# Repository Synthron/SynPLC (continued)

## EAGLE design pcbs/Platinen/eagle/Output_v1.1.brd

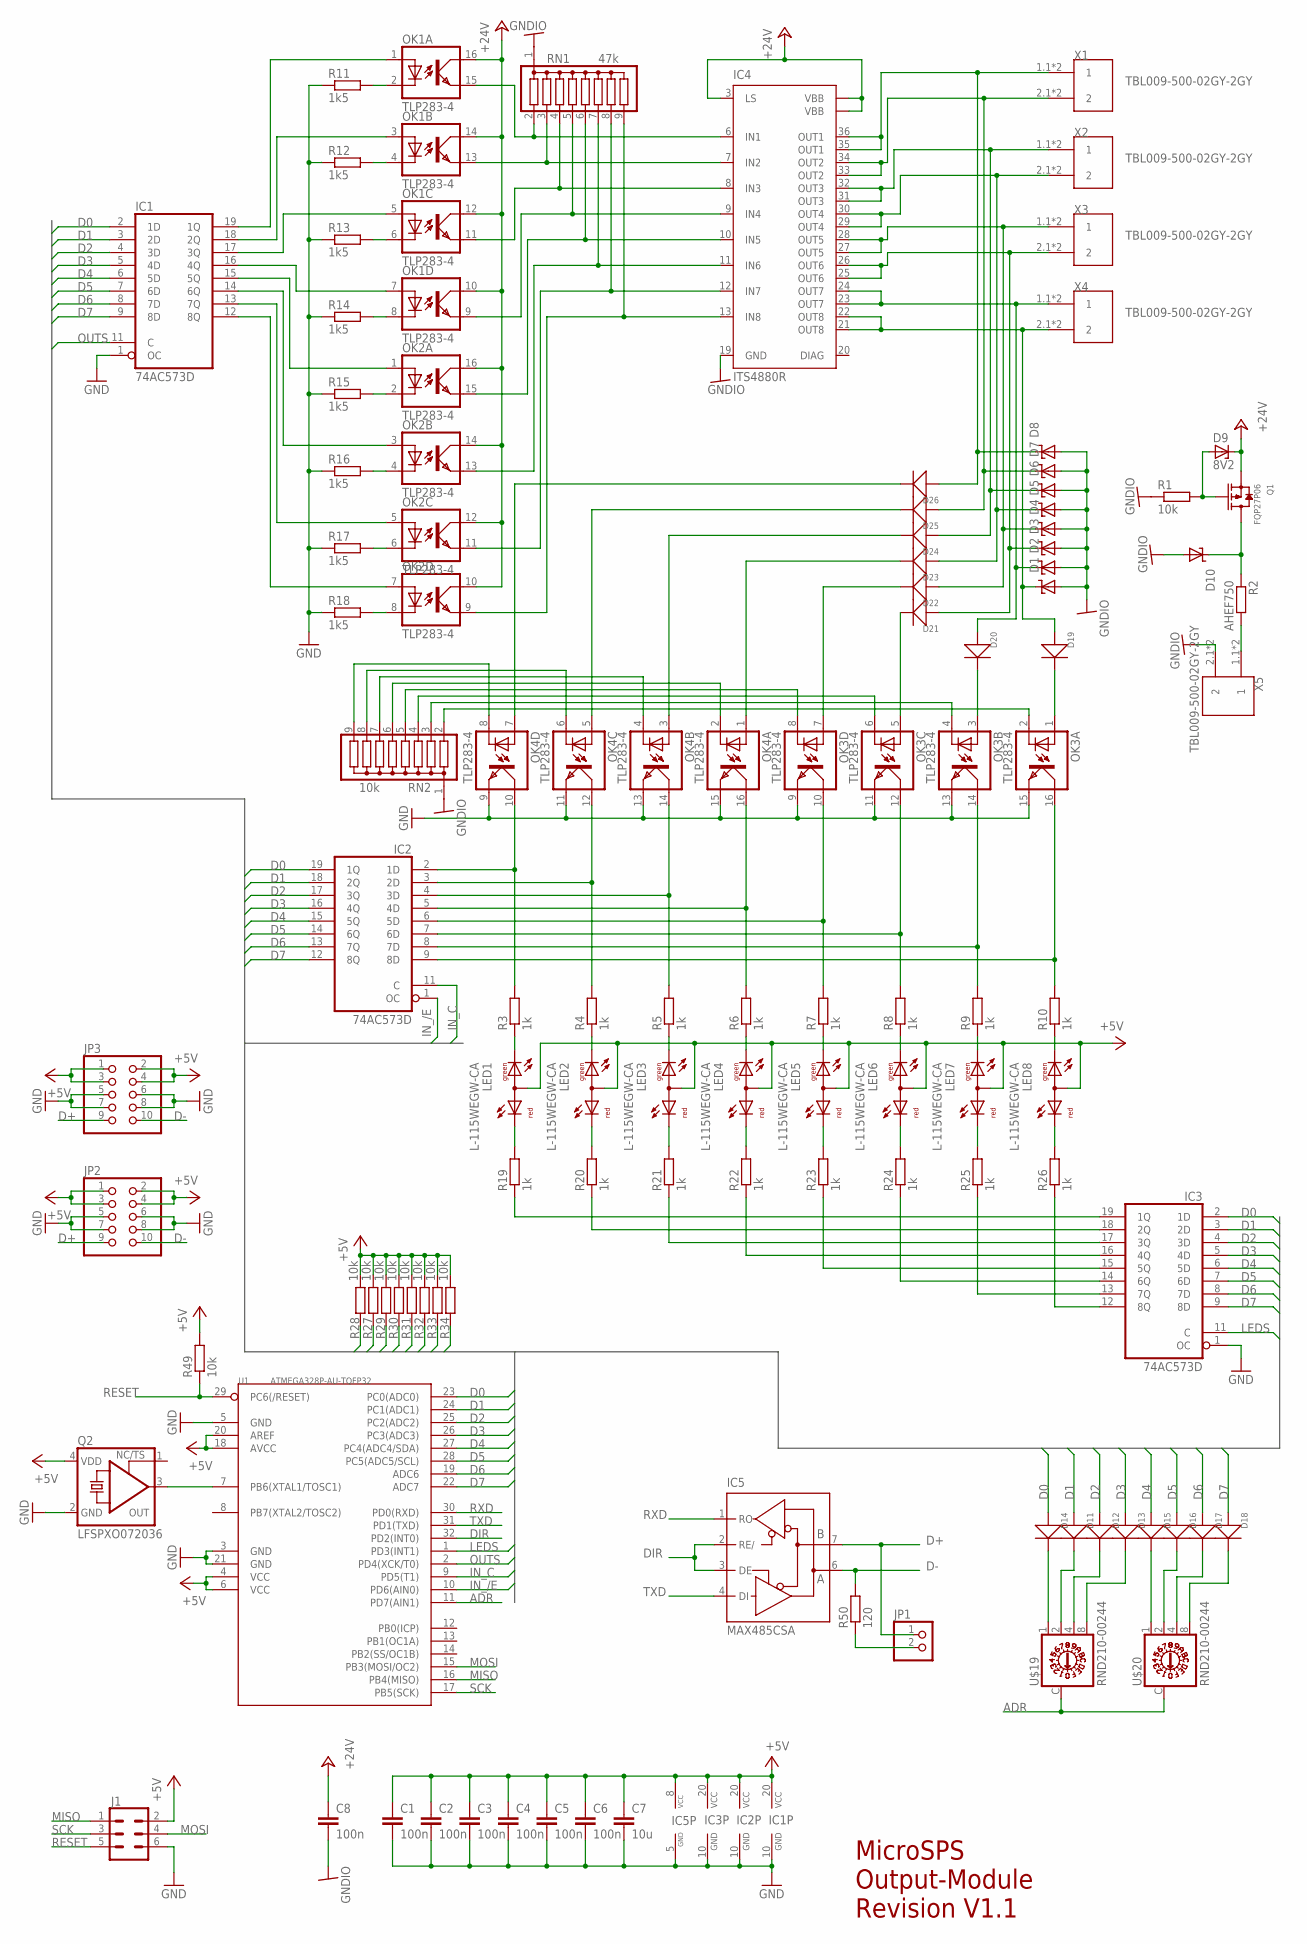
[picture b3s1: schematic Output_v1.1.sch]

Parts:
C1, C2, C3, C4, C5, C6, C8: 100n; C0805
C7: 10u; C0805
D1, D2, D3, D4, D5, D6, D7, D8, D10: SUPPRESSOR-SMBJ; SMBJ
D9: 8V2; SOD80C
D11, D12, D13, D14, D15, D16, D17, D18, D19, D20, D21, D22, D23, D24, D25, D26: DIODE'1N4148-SMD'; LL-34
IC1, IC2, IC3: 74AC573D; SO20W
IC4: ITS4880R; PG-DSO-36
IC5: MAX485CSA; SO08
J1: CONN_03X2FEMALE_SMD; 2X3_SMD
JP1: PINHD-1X2; 1X02
JP2, JP3: PINHD-2X5/90; 2X05/90
LED1, LED2, LED3, LED4, LED5, LED6, LED7, LED8: L-115WEGW-CA; DUOLED-A-3MM
OK1, OK2, OK3, OK4: TLP283-4; MINI-FLAT-16
Q1: FQP27P06; TO-220V
Q2: LFSPXO072036; 5.0X3.2_KXO-56
R1, R27, R28, R29, R30, R31, R32, R33, R34, R49: 10k; R0805
R2: AHEF750; 0204/7
R3, R4, R5, R6, R7, R8, R9, R10, R19, R20, R21, R22, R23, R24, R25, R26: 1k; R0805
R11, R12, R13, R14, R15, R16, R17, R18: 1k5; R0805
R50: 120; R0805
RN1: 47k; SIL9
RN2: 10k; SIL9
U1: ATMEGA328P-AU-TQFP32; TQFP32-0.8-7X7MM
U$19, U$20: RND210-00244
X1, X2, X3, X4, X5: TBL009-500-02GY-2GY

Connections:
+5V: C1.1, C2.1, C3.1, C4.1, C5.1, C6.1, C7.1, IC1.20 (VCC), IC2.20 (VCC), IC3.20 (VCC), IC5.8 (VCC), J1.2, JP2.1, JP2.2, JP2.3, JP2.4, JP3.1, JP3.2, JP3.3, JP3.4, LED1.2 (A), LED2.2 (A), LED3.2 (A), LED4.2 (A), LED5.2 (A), LED6.2 (A), LED7.2 (A), LED8.2 (A), Q2.4 (VDD), R27.2, R28.2, R29.2, R30.2, R31.2, R32.2, R33.2, R34.2, R49.2, U1.4 (VCC), U1.6 (VCC), U1.18 (AVCC), U1.20 (AREF)
+24V: C8.1, D9.C, IC4.3 (LS), IC4.TH@1 (VBB), IC4.TH@2 (VBB), OK1.10 (COL), OK1.12 (COL), OK1.14 (COL), OK1.16 (COL), OK2.10 (COL), OK2.12 (COL), OK2.14 (COL), OK2.16 (COL), Q1.3 (S)
ADR: U1.11 (PD7(AIN1)), U$19.C, U$20.C
D0: D14.A (+), IC1.2 (1D), IC2.19 (1Q), IC3.2 (1D), R28.1, U1.23 (PC0(ADC0))
D1: D11.A (+), IC1.3 (2D), IC2.18 (2Q), IC3.3 (2D), R27.1, U1.24 (PC1(ADC1))
D2: D12.A (+), IC1.4 (3D), IC2.17 (3Q), IC3.4 (3D), R29.1, U1.25 (PC2(ADC2))
D3: D13.A (+), IC1.5 (4D), IC2.16 (4Q), IC3.5 (4D), R30.1, U1.26 (PC3(ADC3))
D4: D15.A (+), IC1.6 (5D), IC2.15 (5Q), IC3.6 (5D), R31.1, U1.27 (PC4(ADC4/SDA))
D5: D16.A (+), IC1.7 (6D), IC2.14 (6Q), IC3.7 (6D), R32.1, U1.28 (PC5(ADC5/SCL))
D6: D17.A (+), IC1.8 (7D), IC2.13 (7Q), IC3.8 (7D), R33.1, U1.19 (ADC6)
D7: D18.A (+), IC1.9 (8D), IC2.12 (8Q), IC3.9 (8D), R34.1, U1.22 (ADC7)
D+: IC5.7 (B), JP1.1, JP2.9, JP3.9
D-: IC5.6 (A), JP2.10, JP3.10, R50.2
DIR: IC5.2 (RE/), IC5.3 (DE), U1.32 (PD2(INT0))
GND: C1.2, C2.2, C3.2, C4.2, C5.2, C6.2, C7.2, IC1.1 (OC), IC1.10 (GND), IC2.10 (GND), IC3.1 (OC), IC3.10 (GND), IC5.5 (GND), J1.6, JP2.5, JP2.6, JP2.7, JP2.8, JP3.5, JP3.6, JP3.7, JP3.8, OK3.9 (EMIT), OK3.11 (EMIT), OK3.13 (EMIT), OK3.15 (EMIT), OK4.9 (EMIT), OK4.11 (EMIT), OK4.13 (EMIT), OK4.15 (EMIT), Q2.2 (GND), R11.1, R12.1, R13.1, R14.1, R15.1, R16.1, R17.1, R18.1, U1.3 (GND), U1.5 (GND), U1.21 (GND)
GNDIO: C8.2, D1.A, D2.A, D3.A, D4.A, D5.A, D6.A, D7.A, D8.A, D10.A, IC4.19 (GND), R1.1, RN1.1, RN2.1, X5.2.1 (2), X5.2.2 (2)
IN_/E: IC2.1 (OC), U1.10 (PD6(AIN0))
IN_C: IC2.11 (C), U1.9 (PD5(T1))
LEDS: IC3.11 (C), U1.1 (PD3(INT1))
MISO: J1.1, U1.16 (PB4(MISO))
MOSI: J1.4, U1.15 (PB3(MOSI/OC2))
unnamed: IC4.6 (IN1), OK1.15 (EMIT), RN1.2
unnamed: IC4.7 (IN2), OK1.13 (EMIT), RN1.3
unnamed: IC4.8 (IN3), OK1.11 (EMIT), RN1.4
unnamed: IC4.9 (IN4), OK1.9 (EMIT), RN1.5
unnamed: IC4.10 (IN5), OK2.15 (EMIT), RN1.6
unnamed: IC4.11 (IN6), OK2.13 (EMIT), RN1.7
unnamed: IC4.12 (IN7), OK2.11 (EMIT), RN1.8
unnamed: IC4.13 (IN8), OK2.9 (EMIT), RN1.9
unnamed: LED1.1 (CG), R3.1
unnamed: LED2.1 (CG), R4.1
unnamed: LED3.1 (CG), R5.1
unnamed: LED4.1 (CG), R6.1
unnamed: LED5.1 (CG), R7.1
unnamed: LED6.1 (CG), R8.1
unnamed: LED7.1 (CG), R9.1
unnamed: LED8.1 (CG), R10.1
unnamed: OK3.2 (C), RN2.2
unnamed: OK3.4 (C), RN2.3
unnamed: OK3.6 (C), RN2.4
unnamed: OK3.8 (C), RN2.5
unnamed: OK4.2 (C), RN2.6
unnamed: OK4.4 (C), RN2.7
unnamed: OK4.6 (C), RN2.8
unnamed: OK4.8 (C), RN2.9
unnamed: D10.C, Q1.2 (D), R2.1
unnamed: D9.A, Q1.1 (G), R1.2
unnamed: D1.C, D19.A (+), IC4.21 (OUT8), IC4.22 (OUT8), X4.2.1 (2), X4.2.2 (2)
unnamed: R2.2, X5.1.1 (1), X5.1.2 (1)
unnamed: D2.C, D20.A (+), IC4.23 (OUT7), IC4.24 (OUT7), X4.1.1 (1), X4.1.2 (1)
unnamed: D3.C, D21.A (+), IC4.25 (OUT6), IC4.26 (OUT6), X3.2.1 (2), X3.2.2 (2)
unnamed: D4.C, D22.A (+), IC4.27 (OUT5), IC4.28 (OUT5), X3.1.1 (1), X3.1.2 (1)
unnamed: D5.C, D23.A (+), IC4.29 (OUT4), IC4.30 (OUT4), X2.2.1 (2), X2.2.2 (2)
unnamed: D6.C, D24.A (+), IC4.31 (OUT3), IC4.32 (OUT3), X2.1.1 (1), X2.1.2 (1)
unnamed: D7.C, D25.A (+), IC4.33 (OUT2), IC4.34 (OUT2), X1.2.1 (2), X1.2.2 (2)
unnamed: D8.C, D26.A (+), IC4.35 (OUT1), IC4.36 (OUT1), X1.1.1 (1), X1.1.2 (1)
unnamed: IC2.2 (1D), OK4.10 (COL), R3.2
unnamed: IC2.3 (2D), OK4.12 (COL), R4.2
unnamed: IC2.4 (3D), OK4.14 (COL), R5.2
unnamed: IC2.5 (4D), OK4.16 (COL), R6.2
unnamed: IC2.6 (5D), OK3.10 (COL), R7.2
unnamed: IC2.7 (6D), OK3.12 (COL), R8.2
unnamed: IC2.8 (7D), OK3.14 (COL), R9.2
unnamed: IC2.9 (8D), OK3.16 (COL), R10.2
unnamed: IC3.19 (1Q), R19.1
unnamed: IC3.18 (2Q), R20.1
unnamed: IC3.17 (3Q), R21.1
unnamed: IC3.16 (4Q), R22.1
unnamed: IC3.15 (5Q), R23.1
unnamed: IC3.14 (6Q), R24.1
unnamed: IC3.13 (7Q), R25.1
unnamed: IC3.12 (8Q), R26.1
unnamed: LED1.3 (CR), R19.2
unnamed: LED2.3 (CR), R20.2
unnamed: OK1.2 (C), R11.2
unnamed: OK1.4 (C), R12.2
unnamed: OK1.6 (C), R13.2
unnamed: OK1.8 (C), R14.2
unnamed: OK2.2 (C), R15.2
unnamed: LED3.3 (CR), R21.2
unnamed: OK2.4 (C), R16.2
unnamed: OK2.6 (C), R17.2
unnamed: OK2.8 (C), R18.2
unnamed: IC1.17 (3Q), OK1.5 (A)
unnamed: IC1.18 (2Q), OK1.3 (A)
unnamed: IC1.19 (1Q), OK1.1 (A)
unnamed: IC1.16 (4Q), OK1.7 (A)
unnamed: IC1.15 (5Q), OK2.1 (A)
unnamed: IC1.14 (6Q), OK2.3 (A)
unnamed: IC1.13 (7Q), OK2.5 (A)
unnamed: IC1.12 (8Q), OK2.7 (A)
unnamed: LED4.3 (CR), R22.2
unnamed: LED5.3 (CR), R23.2
unnamed: LED6.3 (CR), R24.2
unnamed: LED7.3 (CR), R25.2
unnamed: LED8.3 (CR), R26.2
unnamed: D19.C (-), OK3.1 (A)
unnamed: D20.C (-), OK3.3 (A)
unnamed: D21.C (-), OK3.5 (A)
unnamed: D22.C (-), OK3.7 (A)
unnamed: D23.C (-), OK4.1 (A)
unnamed: D24.C (-), OK4.3 (A)
unnamed: D25.C (-), OK4.5 (A)
unnamed: D26.C (-), OK4.7 (A)
unnamed: Q2.3 (OUT), U1.7 (PB6(XTAL1/TOSC1))
unnamed: JP1.2, R50.1
unnamed: D14.C (-), U$19.1
unnamed: D11.C (-), U$19.2
unnamed: D12.C (-), U$19.4
unnamed: D13.C (-), U$19.8
unnamed: D15.C (-), U$20.1
unnamed: D16.C (-), U$20.2
unnamed: D17.C (-), U$20.4
unnamed: D18.C (-), U$20.8
OUTS: IC1.11 (C), U1.2 (PD4(XCK/T0))
RESET: J1.5, R49.1, U1.29 (PC6(/RESET))
RXD: IC5.1 (RO), U1.30 (PD0(RXD))
SCK: J1.3, U1.17 (PB5(SCK))
TXD: IC5.4 (DI), U1.31 (PD1(TXD))

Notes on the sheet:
MicroSPS Output-Module Revision V1.1

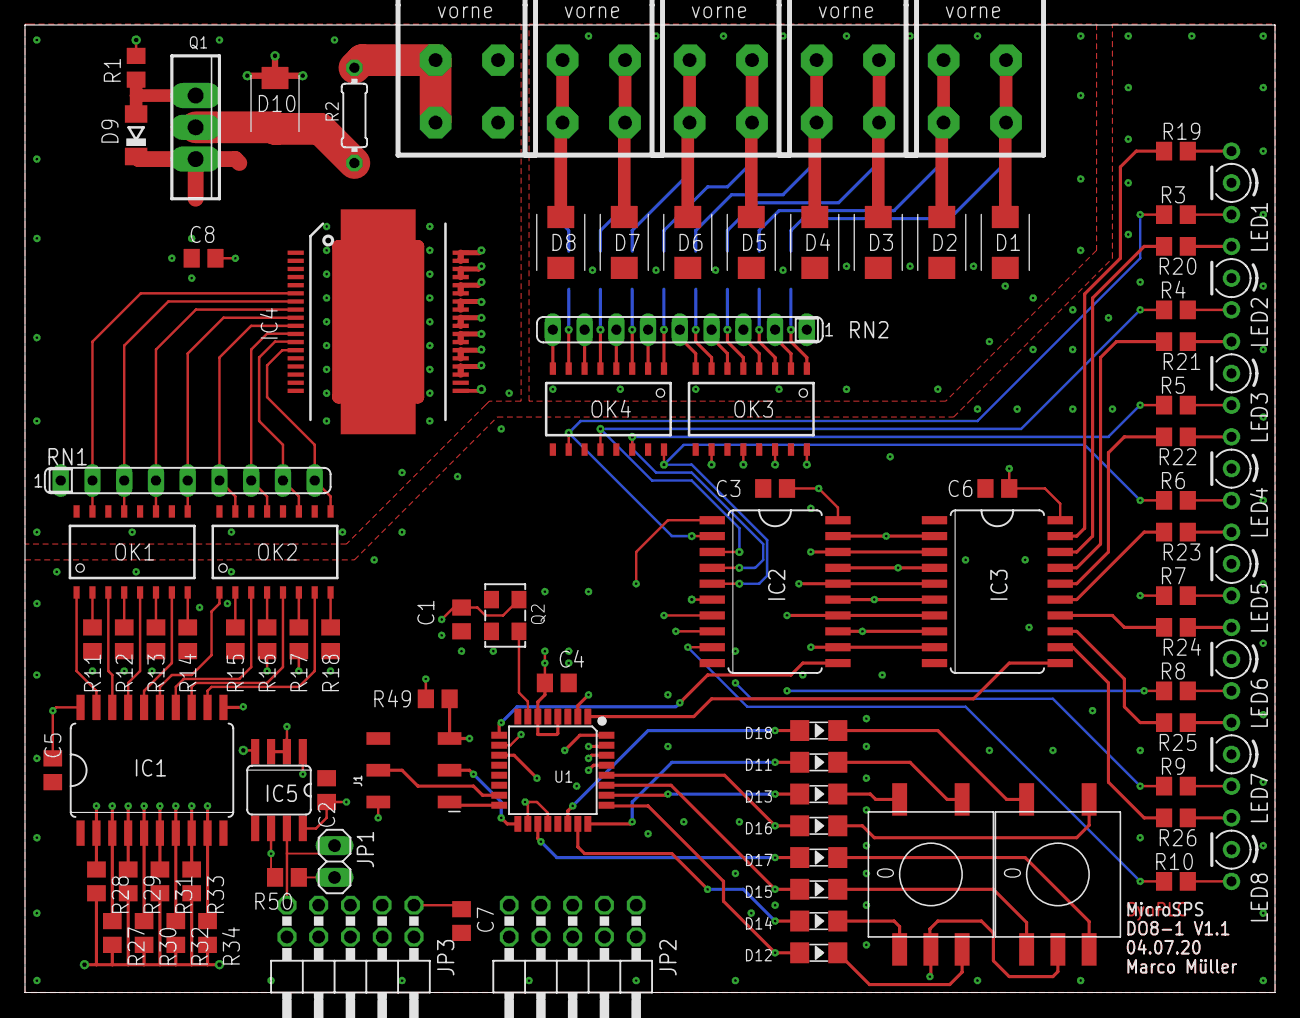
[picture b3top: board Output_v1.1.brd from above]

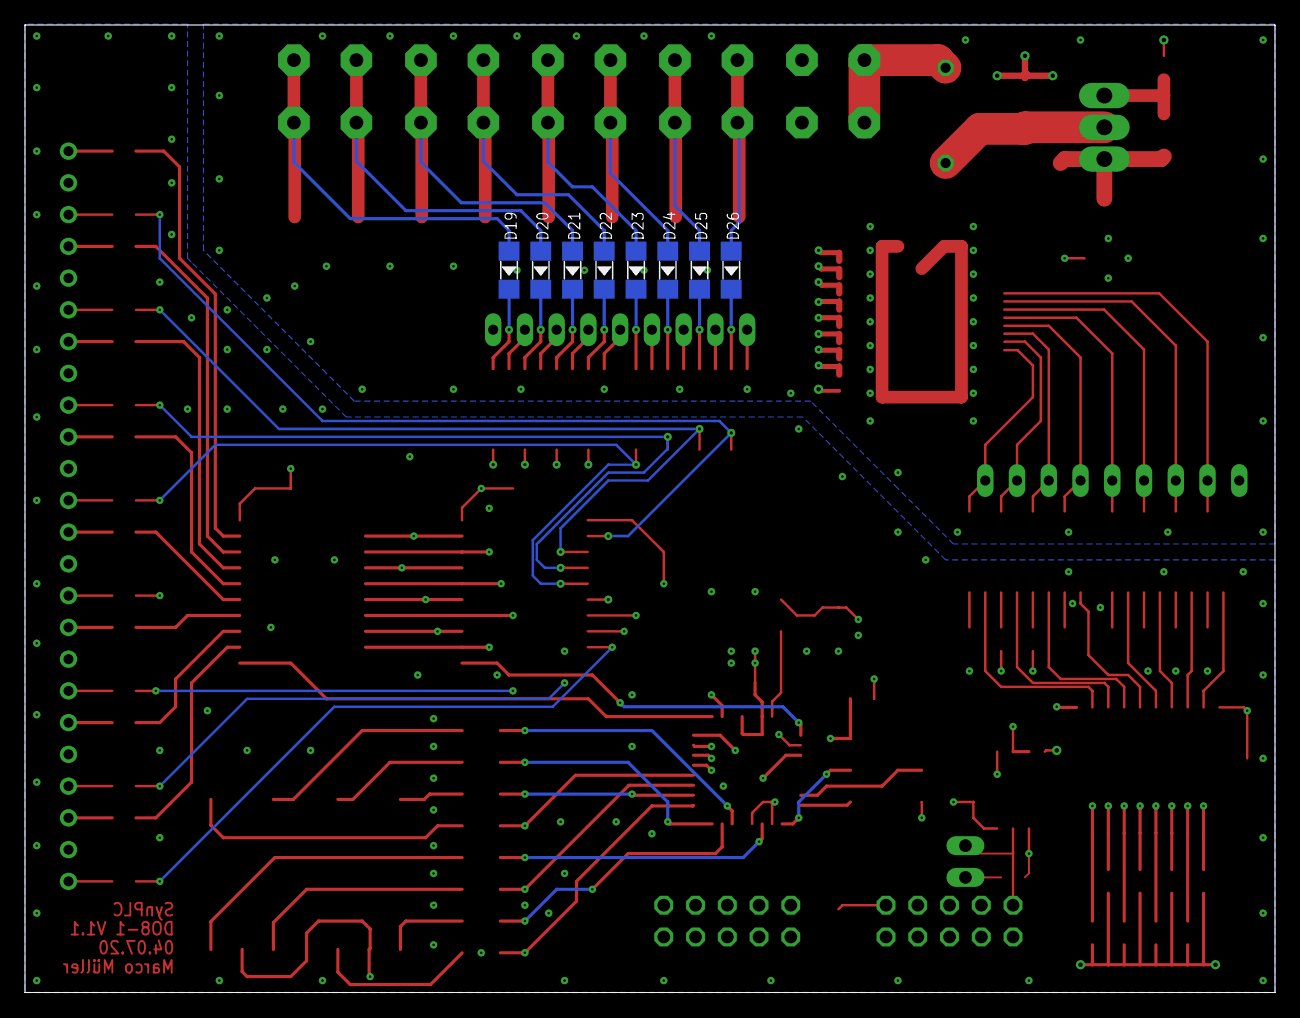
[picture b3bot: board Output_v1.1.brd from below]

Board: 4 copper layers, 100.0 x 77.4 mm, 103 parts (8 on the bottom side), 119 nets.

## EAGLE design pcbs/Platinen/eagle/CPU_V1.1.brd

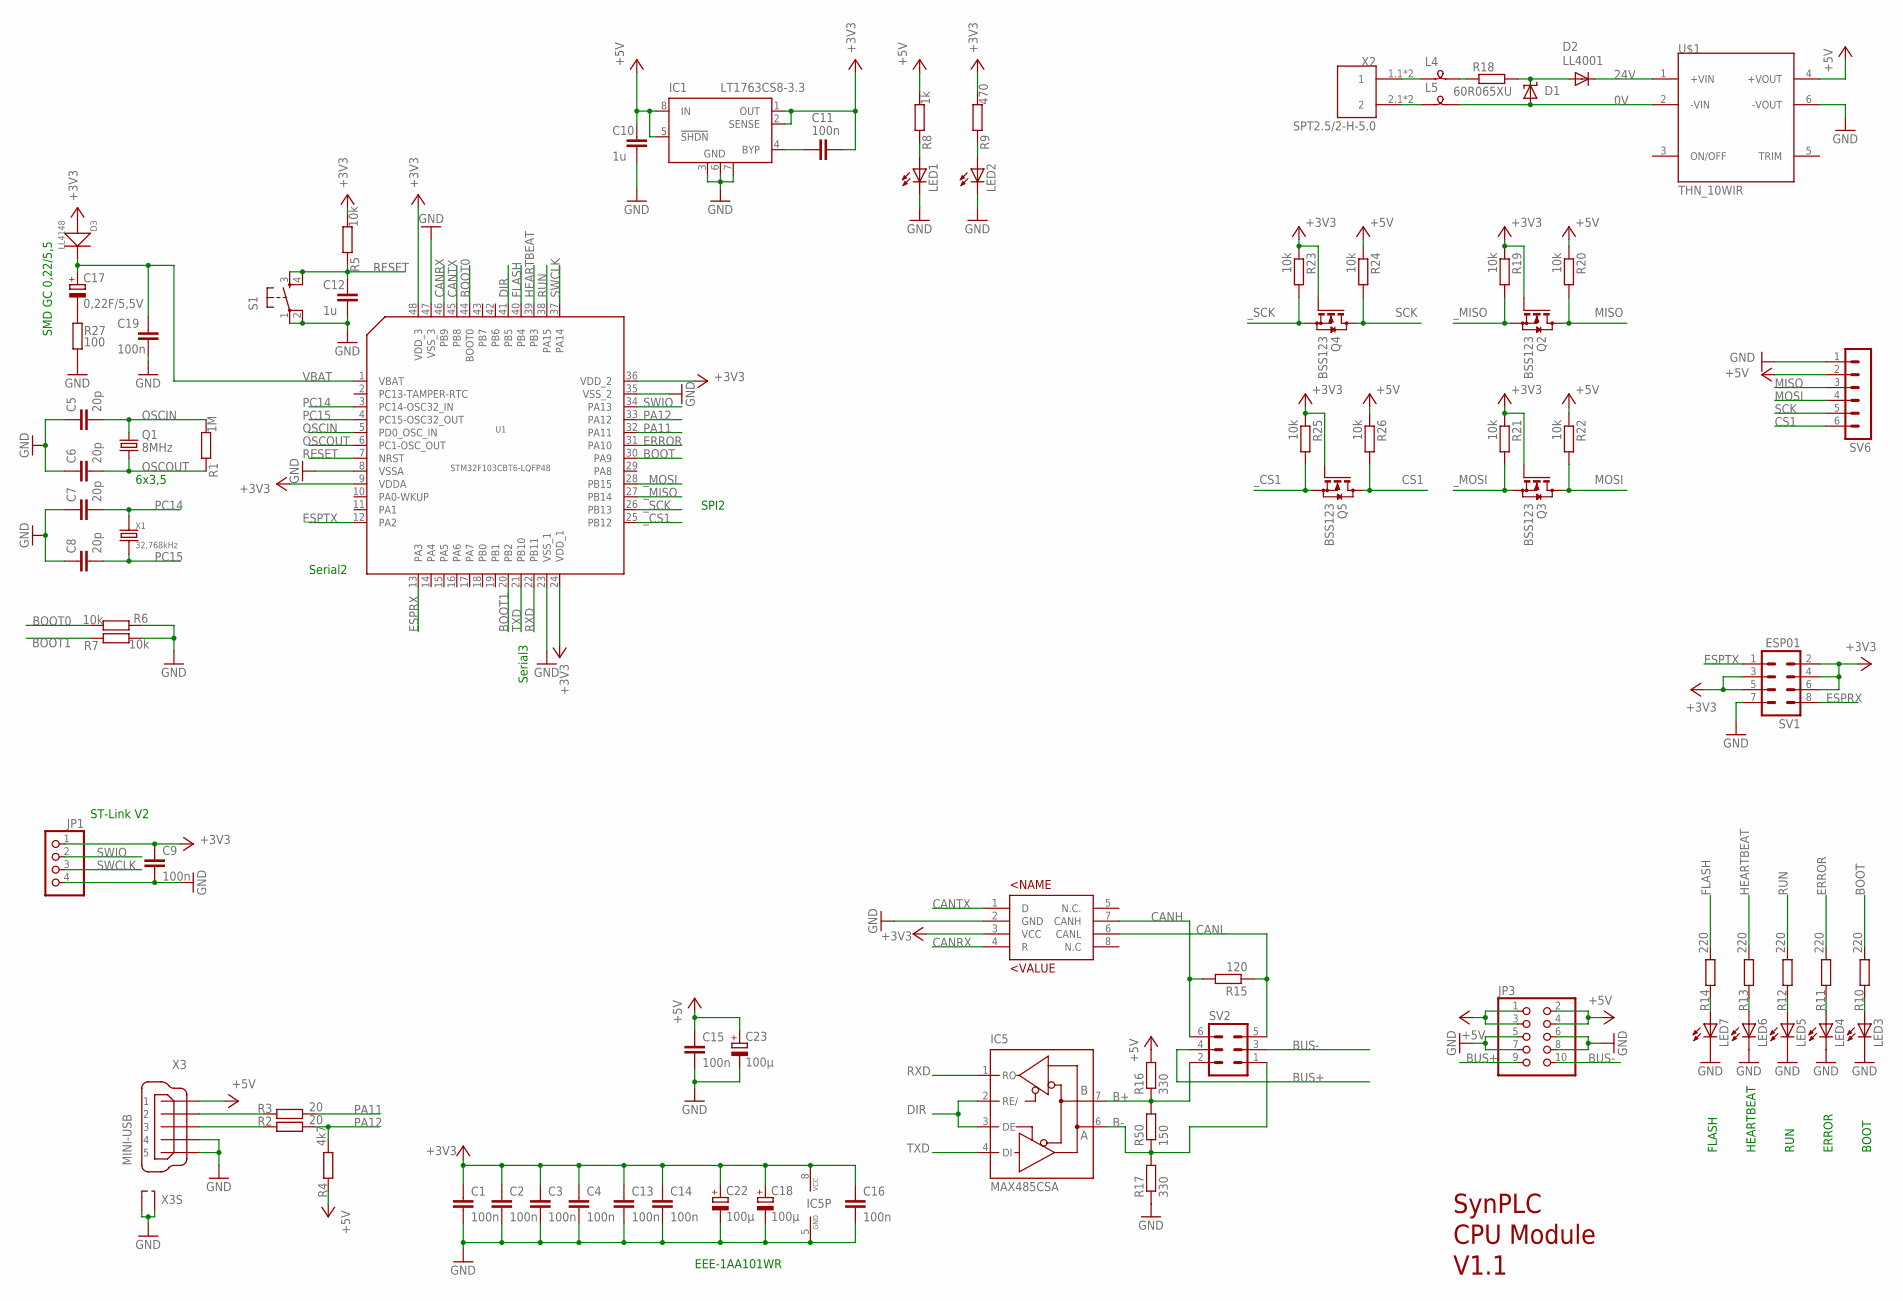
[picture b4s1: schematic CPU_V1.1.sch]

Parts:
C1, C2, C3, C4, C9, C11, C13, C14, C19: 100n; C0805K
C5, C6, C7, C8: 20p; C0805K
C10, C12: 1u; C0805K
C15, C16: 100n; C0805
C17: 0,22F/5,5V; PANASONIC_G
C18, C22, C23: 100µ; 153CLV-0505
D1: SUPPRESSOR-SMBJ; SMBJ
D2: LL4001; SOD-123_MINI-SMA
D3: LL4148; LL-34
IC1: LT1763CS8-3.3; SOIC8
IC5: MAX485CSA; SO08
JP1: PINHD-1X4/90; 1X04/90
JP3: PINHD-2X5/90; 2X05/90
L4, L5: SM-B5
LED1, LED2: LEDSML0805; SML0805
LED3, LED4, LED5, LED6, LED7: LED3MM
Q1: 8MHz; 11.4X4.5
Q2, Q3, Q4, Q5: BSS123; SOT23
R1: 1M; R0805
R2, R3: 20; R0805
R4: 4k7; R0805
R5, R6, R7, R19, R20, R21, R22, R23, R24, R25, R26: 10k; R0805
R8: 1k; R0805
R9: 470; R0805
R10, R11, R12, R13, R14: 220; R0805
R15: 120; R0805
R16, R17: 330; R0805
R18: 60R065XU; 0204/5
R27: 100; R0805
R50: 150; R0805
S1: TAC_SWITCHPTH; TACTILE-PTH
SV1: ESP01; MA04-2
SV2: MA03-2
SV6: MA06-1
U1: STM32F103CBT6-LQFP48; LQFP48-0.5-7X7MM
U$1: THN_10WIR; THN10WIR
U$3: SN65HVD232; SO-08
X1: 32,768kHz; X2-2.0-D9.1XL3.3MM
X2: SPT2.5/2-H-5.0; SPT2
X3: MINI-USB; 32005-601

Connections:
0V: D1.A, L5.1, U$1.2 (-VIN)
24V: D2.C, U$1.1 (+VIN)
+3V3: C1.1, C2.1, C3.1, C4.1, C9.1, C11.1, C13.1, C14.1, C16.1, C18.+, C22.+, D3.A (+), IC1.1 (OUT), IC1.2 (SENSE), IC5.8 (VCC), JP1.1, Q2.1 (G), Q3.1 (G), Q4.1 (G), Q5.1 (G), R5.2, R9.2, R19.1, R21.1, R23.1, R25.1, SV1.2, SV1.3, SV1.4, SV1.5, SV1.6, U1.9 (VDDA), U1.24 (VDD_1), U1.36 (VDD_2), U1.48 (VDD_3), U$3.3 (VCC)
+5V: C10.1, C15.1, C23.+, IC1.5 (!SHDN), IC1.8 (IN), JP3.1, JP3.2, JP3.3, JP3.4, R4.1, R8.2, R16.2, R20.1, R22.1, R24.1, R26.1, SV6.2, U$1.4 (+VOUT), X3.1
B+: IC5.7 (B), R16.1, R50.2, SV2.2
B-: IC5.6 (A), R17.2, R50.1, SV2.1
BOOT: R10.2, U1.30 (PA9)
BOOT0: R6.2, U1.44 (BOOT0)
BOOT1: R7.1, U1.20 (PB2)
BUS+: JP3.9, SV2.4
BUS-: JP3.10, SV2.3
CANH: R15.2, SV2.6, U$3.7 (CANH)
CANL: R15.1, SV2.5, U$3.6 (CANL)
CANRX: U1.46 (PB9), U$3.4 (R)
CANTX: U1.45 (PB8), U$3.1 (D)
CS1: Q5.3 (D), R26.2, SV6.6
DIR: IC5.2 (RE/), IC5.3 (DE), U1.41 (PB5)
ERROR: R11.2, U1.31 (PA10)
ESPRX: SV1.8, U1.13 (PA3)
ESPTX: SV1.1, U1.12 (PA2)
FLASH: R14.2, U1.40 (PB4)
GND: C1.2, C2.2, C3.2, C4.2, C5.1, C6.1, C7.1, C8.1, C9.2, C10.2, C12.2, C13.2, C14.2, C15.2, C16.2, C18.-, C19.2, C22.-, C23.-, IC1.3 (GND), IC1.6 (GND), IC1.7 (GND), IC5.5 (GND), JP1.4, JP3.5, JP3.6, JP3.7, JP3.8, LED1.C, LED2.C, LED3.K (C), LED4.K (C), LED5.K (C), LED6.K (C), LED7.K (C), R6.1, R7.2, R17.1, R27.1, S1.1, S1.2, SV1.7, SV6.1, U1.8 (VSSA), U1.23 (VSS_1), U1.35 (VSS_2), U1.47 (VSS_3), U$1.6 (-VOUT), U$3.2 (GND), X3.4, X3.5, X3.M1 (S1), X3.M2 (S2)
HEARTBEAT: R13.2, U1.39 (PB3)
MISO: Q2.3 (D), R20.2, SV6.3
MOSI: Q3.3 (D), R22.2, SV6.4
unnamed: R3.1, X3.2
unnamed: R2.1, X3.3
unnamed: C11.2, IC1.4 (BYP)
unnamed: LED2.A, R9.1
unnamed: LED1.A, R8.1
unnamed: C17.-, R27.2
unnamed: LED3.A, R10.1
unnamed: LED4.A, R11.1
unnamed: LED5.A, R12.1
unnamed: LED6.A, R13.1
unnamed: LED7.A, R14.1
unnamed: L4.2, X2.1.1 (1), X2.1.2 (1)
unnamed: L5.2, X2.2.1 (2), X2.2.2 (2)
unnamed: L4.1, R18.1
unnamed: D1.C, D2.A, R18.2
OSCIN: C5.2, Q1.2, R1.2, U1.5 (PD0_OSC_IN)
OSCOUT: C6.2, Q1.1, R1.1, U1.6 (PC1-OSC_OUT)
PA11: R3.2, U1.32 (PA11)
PA12: R2.2, R4.2, U1.33 (PA12)
PC14: C7.2, U1.3 (PC14-OSC32_IN), X1.2
PC15: C8.2, U1.4 (PC15-OSC32_OUT), X1.1
RESET: C12.1, R5.1, S1.3, S1.4, U1.7 (NRST)
RUN: R12.2, U1.38 (PA15)
RXD: IC5.1 (RO), U1.22 (PB11)
SCK: Q4.3 (D), R24.2, SV6.5
SWCLK: JP1.3, U1.37 (PA14)
SWIO: JP1.2, U1.34 (PA13)
TXD: IC5.4 (DI), U1.21 (PB10)
VBAT: C17.+, C19.1, D3.C (-), U1.1 (VBAT)
_CS1: Q5.2 (S), R25.2, U1.25 (PB12)
_MISO: Q2.2 (S), R19.2, U1.27 (PB14)
_MOSI: Q3.2 (S), R21.2, U1.28 (PB15)
_SCK: Q4.2 (S), R23.2, U1.26 (PB13)

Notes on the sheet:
SynPLC CPU Module V1.1
ST-Link V2
BOOT
ERROR
RUN
HEARTBEAT
FLASH
EEE-1AA101WR
Serial2
SPI2
Serial3
SMD GC 0,22/5,5
6x3,5

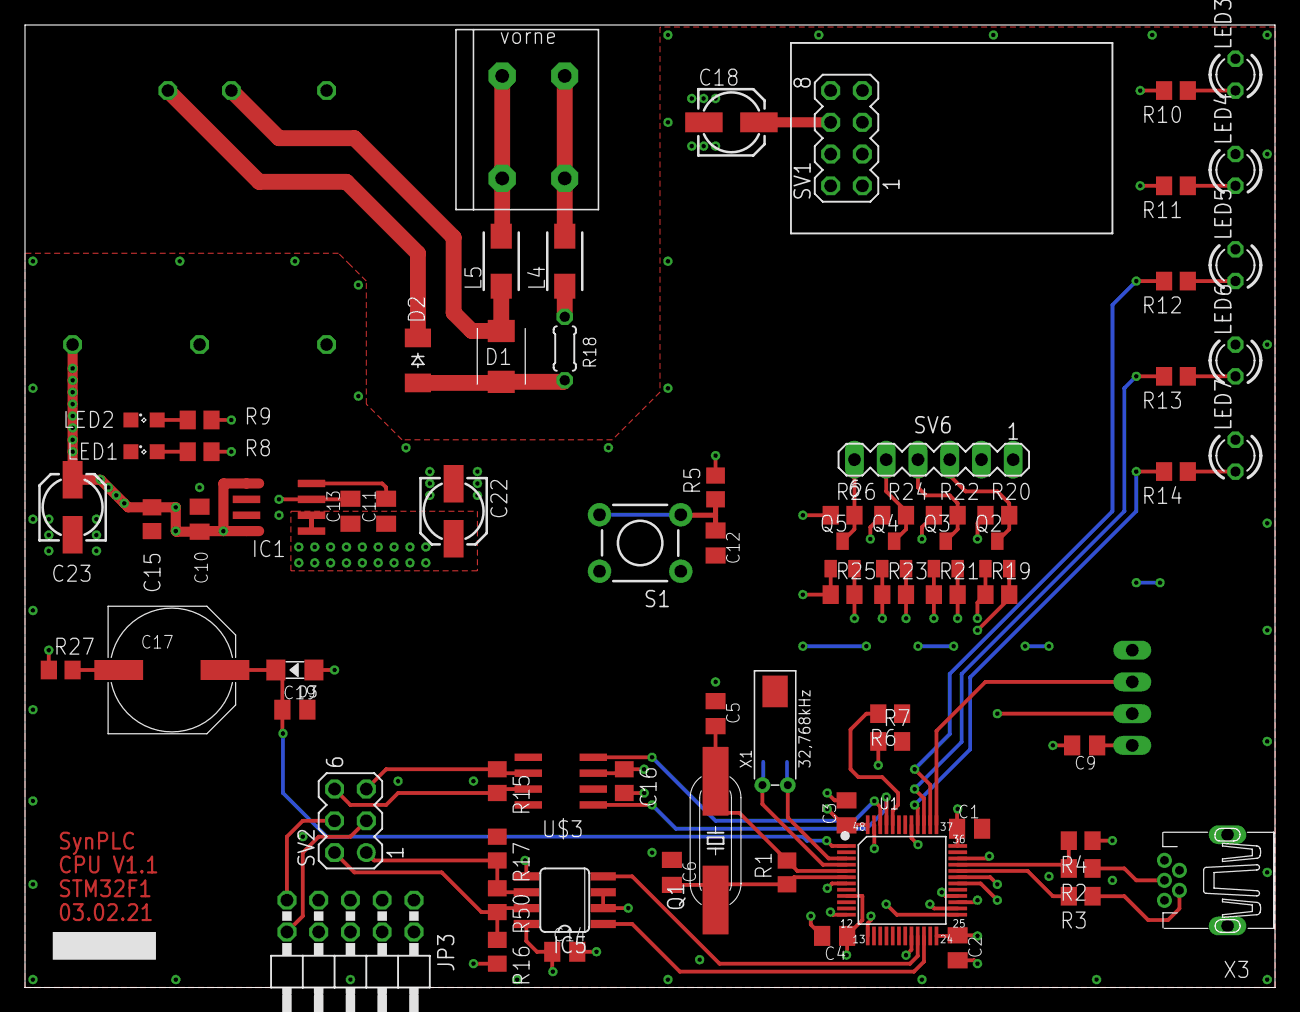
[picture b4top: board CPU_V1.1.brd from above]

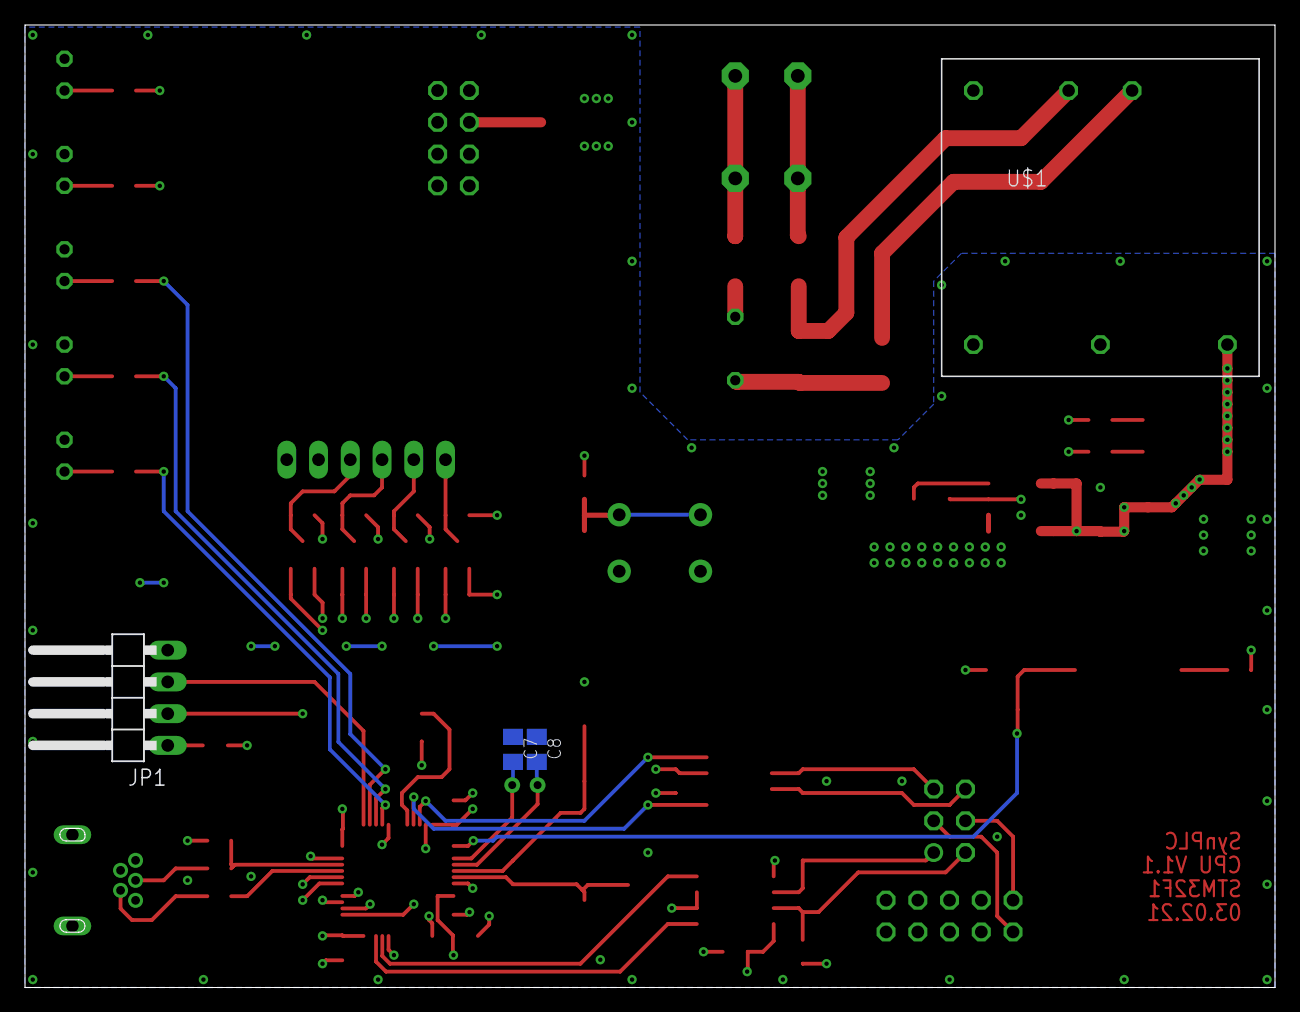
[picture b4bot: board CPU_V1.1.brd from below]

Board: 4 copper layers, 100.0 x 77.0 mm, 80 parts (4 on the bottom side), 58 nets.

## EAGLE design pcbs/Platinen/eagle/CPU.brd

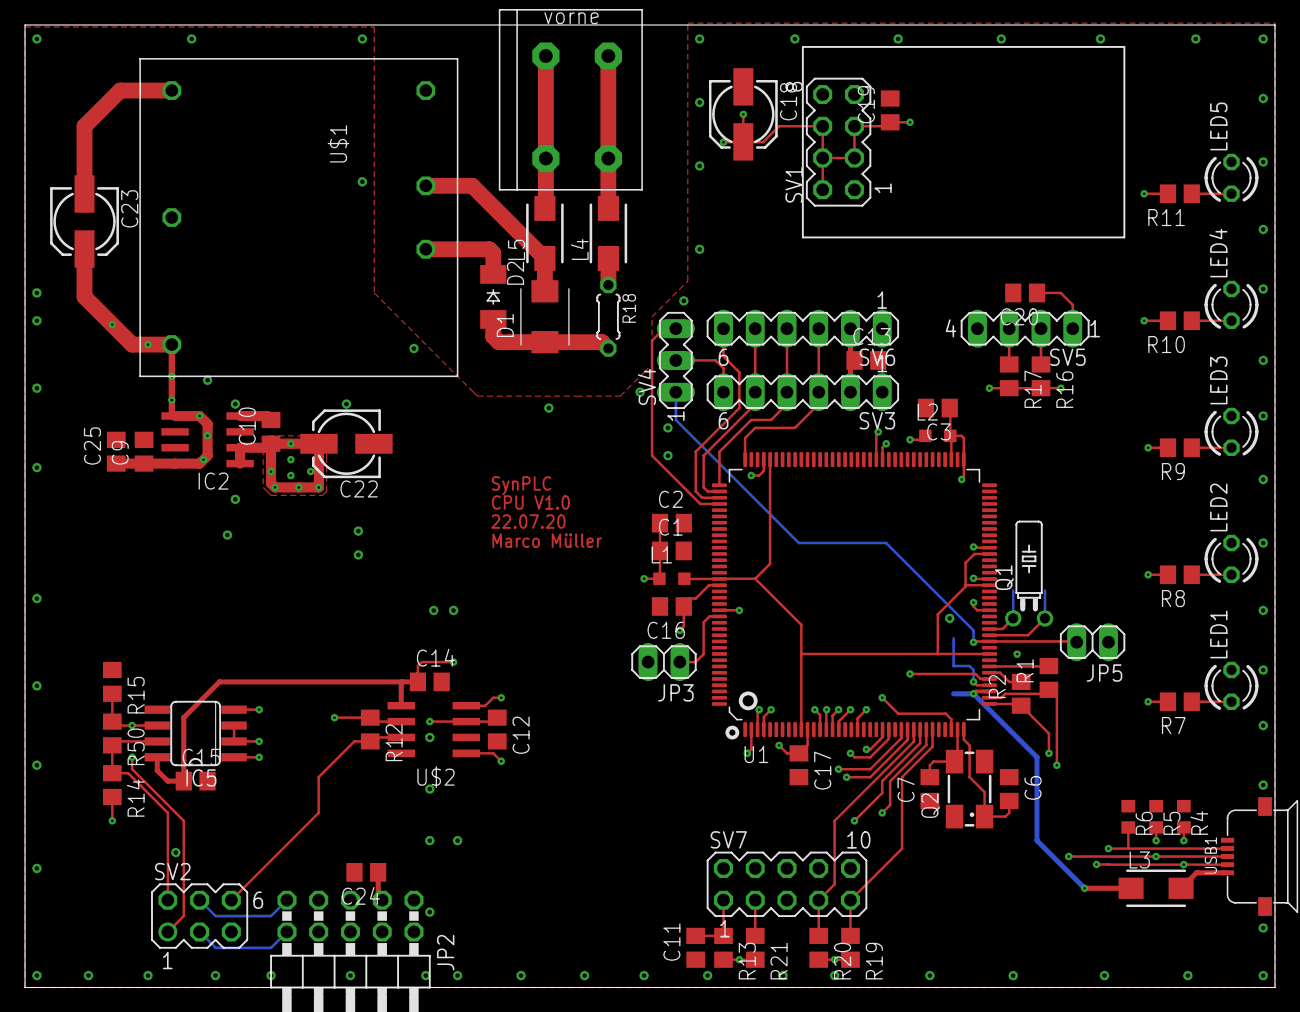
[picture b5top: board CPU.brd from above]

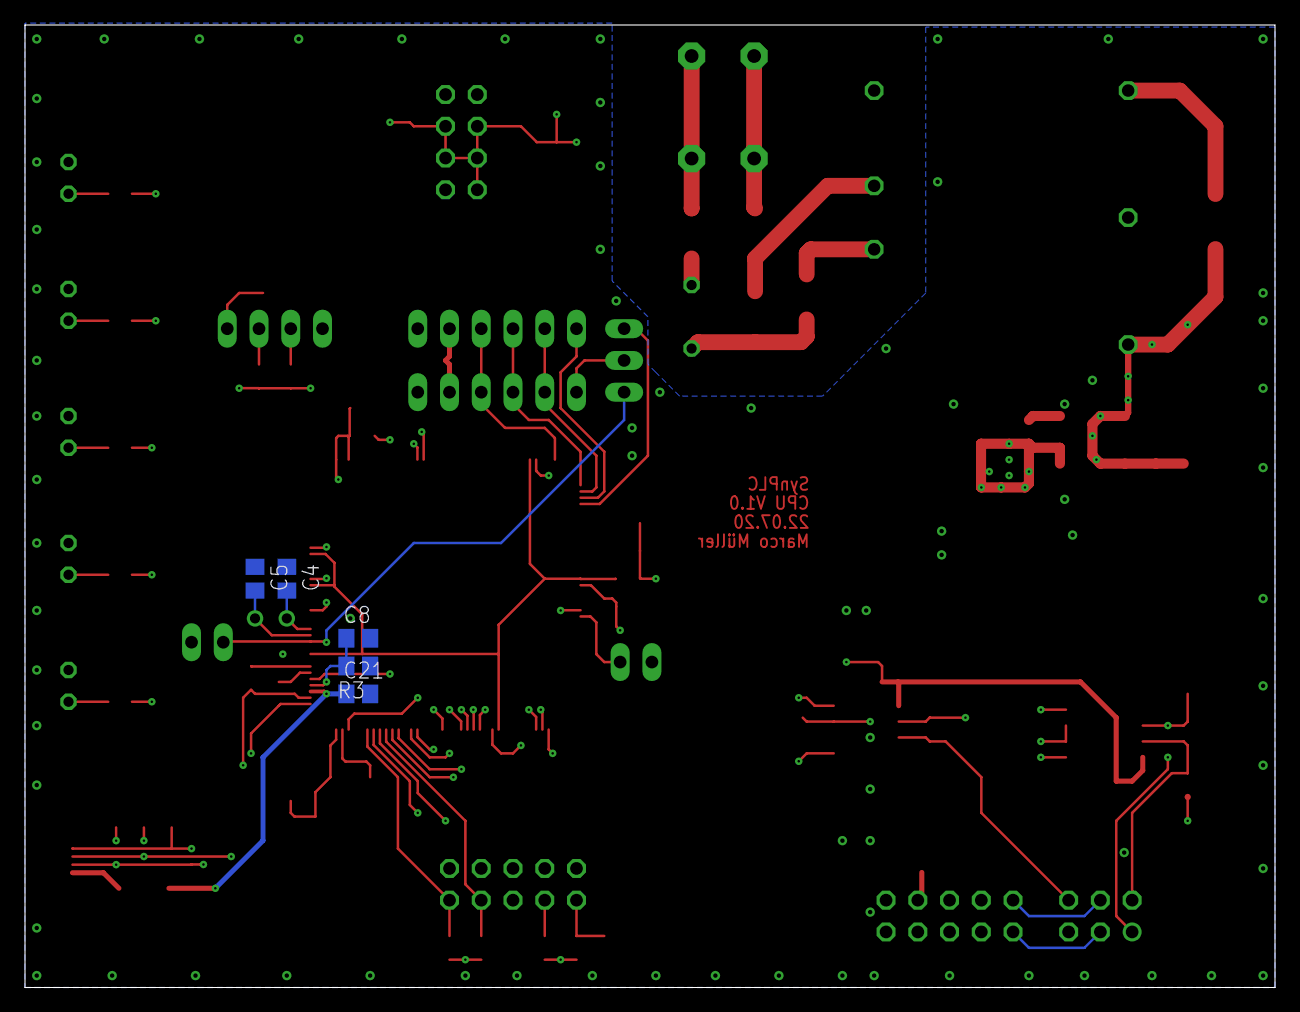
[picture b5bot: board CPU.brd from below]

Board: 4 copper layers, 100.0 x 77.0 mm, 78 parts (5 on the bottom side), 62 nets.

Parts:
C1, C3, C10, C11, C12, C13, C14, C15, C16, C17, C19, C20, C21, C24, C25: 100n; C0805
C2: 10µ; C0805
C4, C5, C6, C7, C8: 22p; C0805
C9: 1µ; C0805
C18, C22, C23: 100µ; 153CLV-0505
D1: SMBJ
D2: CGRM4001-G; SOD-123_MINI-SMA
IC2: LT1763CS8-3.3; SOIC8
IC5: MAX485CSA; SO08
JP2: 2X05/90
JP3, JP5: 1X02
L1, L2: MH2029-300Y; L2012C
L3, L4, L5: SM-B5
LED1, LED2, LED3, LED4, LED5: LED3MM
Q1: 428-200125-PL08; TC26H
Q2: 406I35E12M00000; CTS406
R1, R2: 39R 1%; R0805
R3: 6k8 1%; R0805
R4, R5, R6: CG0603MLC-05E; R0603
R7, R8, R9, R10, R11: 220; R0805
R12: 120; R0805
R13: 10k; R0805
R14, R15: 330; R0805
R16, R17: 3k3; R0805
R18: 60R065XU; 0204/5
R19, R20, R21: 100k; R0805
R50: 150; R0805
SV1: ESP01; MA04-2
SV2: MA03-2
SV3, SV6: MA06-1
SV4: MA03-1
SV5: MA04-1
SV7: MA05-2
U1: ATSAM3X8EA-AU-ND-LQFP144; LQFP144-0.5-20X20M
U$1: THN_10WIR; THN10WIR
U$2: TCAN1044VDRQ1; SO-08
USB1: ST-USB-001L; MICRO-USB5+2P-SMD-0.65
X1: SPT2.5/2-H-5.0; SPT2

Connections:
0V: D1.A, L5.1, U$1.2
4_/CS: SV4.3, U1.112
10_/CS1: SV6.6, U1.111
24V: D2.C, U$1.1
25_BOOT: R7.2, U1.13
26_ERROR: R8.2, U1.14
27_RUN: R9.2, U1.15
28_HEARTBEAT: R10.2, U1.16
29_FLASH: R11.2, U1.19
+3V3: C10.1, C14.1, C15.1, C16.1, C17.1, C18.+, C19.1, C20.1, C22.+, IC2.1, IC2.2, IC5.8, JP3.2, L2.1, R13.2, R16.2, R17.2, R19.2, R20.2, R21.2, SV1.2, SV1.3, SV1.4, SV1.5, SV1.6, SV5.1, SV7.10, U1.11, U1.52, U1.57, U1.62, U1.105, U1.125, U$2.5
+5V: C9.1, C12.1, C13.1, C23.+, C24.1, C25.1, IC2.5, IC2.8, JP2.1, JP2.2, JP2.3, JP2.4, R14.2, SV3.2, SV6.2, U$1.4, U$2.3
B+: IC5.7, R14.1, R50.2, SV2.2
B-: IC5.6, R15.2, R50.1, SV2.1
BUS+: JP2.9, SV2.4
BUS-: JP2.10, SV2.3
CANH: R12.2, SV2.6, U$2.7
CANL: R12.1, SV2.5, U$2.6
CANRX: U1.24, U$2.4
CANTX: U1.23, U$2.1
CS: SV3.6, SV4.2
D+: R2.1, R5.2, U1.37, USB1.3
D-: R1.1, R4.2, U1.38, USB1.2
DIR: IC5.2, IC5.3, U1.26
ESPRX: SV1.8, U1.3
ESPTX: SV1.1, U1.4
GND: C1.2, C2.2, C3.2, C4.1, C5.1, C6.1, C7.1, C8.2, C9.2, C11.1, C12.2, C13.2, C14.2, C15.2, C16.2, C17.2, C18.-, C19.2, C20.2, C21.2, C22.-, C23.-, C24.2, C25.2, IC2.3, IC2.6, IC2.7, IC5.5, JP2.5, JP2.6, JP2.7, JP2.8, JP5.1, LED1.K, LED2.K, LED3.K, LED4.K, LED5.K, R3.1, R4.1, R5.1, R6.1, R15.1, SV1.7, SV3.1, SV5.4, SV6.1, SV7.2, SV7.6, SV7.8, U1.12, U1.33, U1.44, U1.46, U1.54, U1.58, U1.74, U1.106, U1.126, U$1.6, U$2.2, U$2.8, USB1.5, USB1.6, USB1.7
ID: R6.2, U1.129, USB1.4
MISO: SV3.3, SV6.3, U1.108
MOSI: SV3.4, SV6.4, U1.109
unnamed: L1.2, U1.10, U1.45, U1.56, U1.61, U1.104, U1.124
unnamed: C1.1, C2.1, L1.1, U1.34
unnamed: C3.1, L2.2, U1.41, U1.73, U1.75
unnamed: C5.2, Q1.2, U1.48
unnamed: C4.2, Q1.1, U1.49
unnamed: C8.1, R3.2, U1.40
unnamed: JP3.1, U1.130
unnamed: C10.2, IC2.4
unnamed: C7.2, Q2.3, U1.35
unnamed: C6.2, Q2.1, U1.36
unnamed: LED1.A, R7.1
unnamed: LED2.A, R8.1
unnamed: R2.2, U1.42
unnamed: R1.2, U1.43
unnamed: LED3.A, R9.1
unnamed: LED4.A, R10.1
unnamed: LED5.A, R11.1
unnamed: L3.2, USB1.1
unnamed: L4.2, X1.1.1, X1.1.2
unnamed: L5.2, X1.2.1, X1.2.2
unnamed: L4.1, R18.1
unnamed: D1.C, D2.A, R18.2
RESET: C11.2, JP5.2, R13.1, SV4.1, SV7.1, U1.47
RXD: IC5.1, U1.27
SCK: SV3.5, SV6.5, U1.110
SCL: R17.1, SV5.3, U1.87
SDA: R16.1, SV5.2, U1.86
TCK: R20.1, SV7.7, U1.28
TDI: R21.1, SV7.3, U1.29
TDO: SV7.5, U1.30
TMS: R19.1, SV7.9, U1.31
TXD: IC5.4, U1.2
VBUS: C21.1, L3.1, U1.39

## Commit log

2020-07-05 add pcb files
2020-07-06 add casing for DIN-Rail
2020-07-07 adding step-files
2020-07-08 update case file
2020-07-08 Deleted din-rail case/Gehaeuse.FCStd
2020-07-08 update name in case
2020-07-08 update name
2020-07-09 add tolerances to case
2020-07-17 update case with logo
2020-07-17 adding documentation
2020-07-26 Update pcbs/CPU_2020-07-26_unfinished.zip, pcbs/analog_out_2020-07-24.zip, pcbs/Output_v1.1_2020-07-24.zip, pcbs/Input_v1.0_2020-07-24.zip files
2020-07-31 update doc
2020-08-12 create code for DI
2020-08-14 update code
2020-08-20 update firmwares
2021-02-06 update Documentation
2021-02-07 update docs
2021-03-29 update rs485-spec and test-code
2021-04-03 update doc with RS485-protocol
2021-06-14 Bigger update 14.06.21
    updated PCB files
    updated documentation
    updated RS485 protocol
    updated firmwares
2021-06-15 update layout for AI
2021-06-15 fixed DRC on AO
2021-06-16 review AI V1 and AO V2
2021-06-17 updated files
2021-06-17 design of XT V1
2021-06-17 bugfixes on PCBs
2021-06-17 update simulation file
2021-06-17 Redesign XT V1
2021-06-18 start rework of DI and DO
2021-06-20 PCB update
2021-06-20 finalizing DO8_V1.2 Routing
2021-06-21 update DO8
2021-06-21 finalize DO8 layout
2021-06-21 finished layouts
2021-06-28 fix error in Schematic
2021-07-04 create todos
2021-07-05 started revs
2021-07-06 complete reviews from dave
2021-07-12 start translating documentation to english
2021-07-12 work on doc
2021-07-13 start XP module
2021-10-15 greate gerbers, plot schematics
2021-10-31 finalize PCBs; start STM32 code
2021-11-07 uodate Case CAD
2021-12-06 quick update
2022-05-15 backup commit
2022-05-20 added STM-Code
2022-05-20 DO code working!
2022-05-24 update RS485 lib
2023-04-26 Overhaul
2023-04-30 CPU Update Finish CPU V2 Design and finish CPU PiggyBack Board
2023-04-30 Overhaul Repo Cleanup Case for new CPU PiggyBack Update
2023-04-30 case design for new CPU with piggyback
2023-05-02 CPU V2 Review
2023-06-11 GPN Update: Rewrote RS485 protocol with interrupts
2024-03-05 repo transfer
2025-06-28 update rs485 protocols, debug bus garbage collection, get AO running, get AI codebase
2026-05-25 general update (too stretched out to remember what I all did)
2026-06-02 add agents
